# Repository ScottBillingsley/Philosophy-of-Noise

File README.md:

# Philosophy-of-Noise-readme.txt

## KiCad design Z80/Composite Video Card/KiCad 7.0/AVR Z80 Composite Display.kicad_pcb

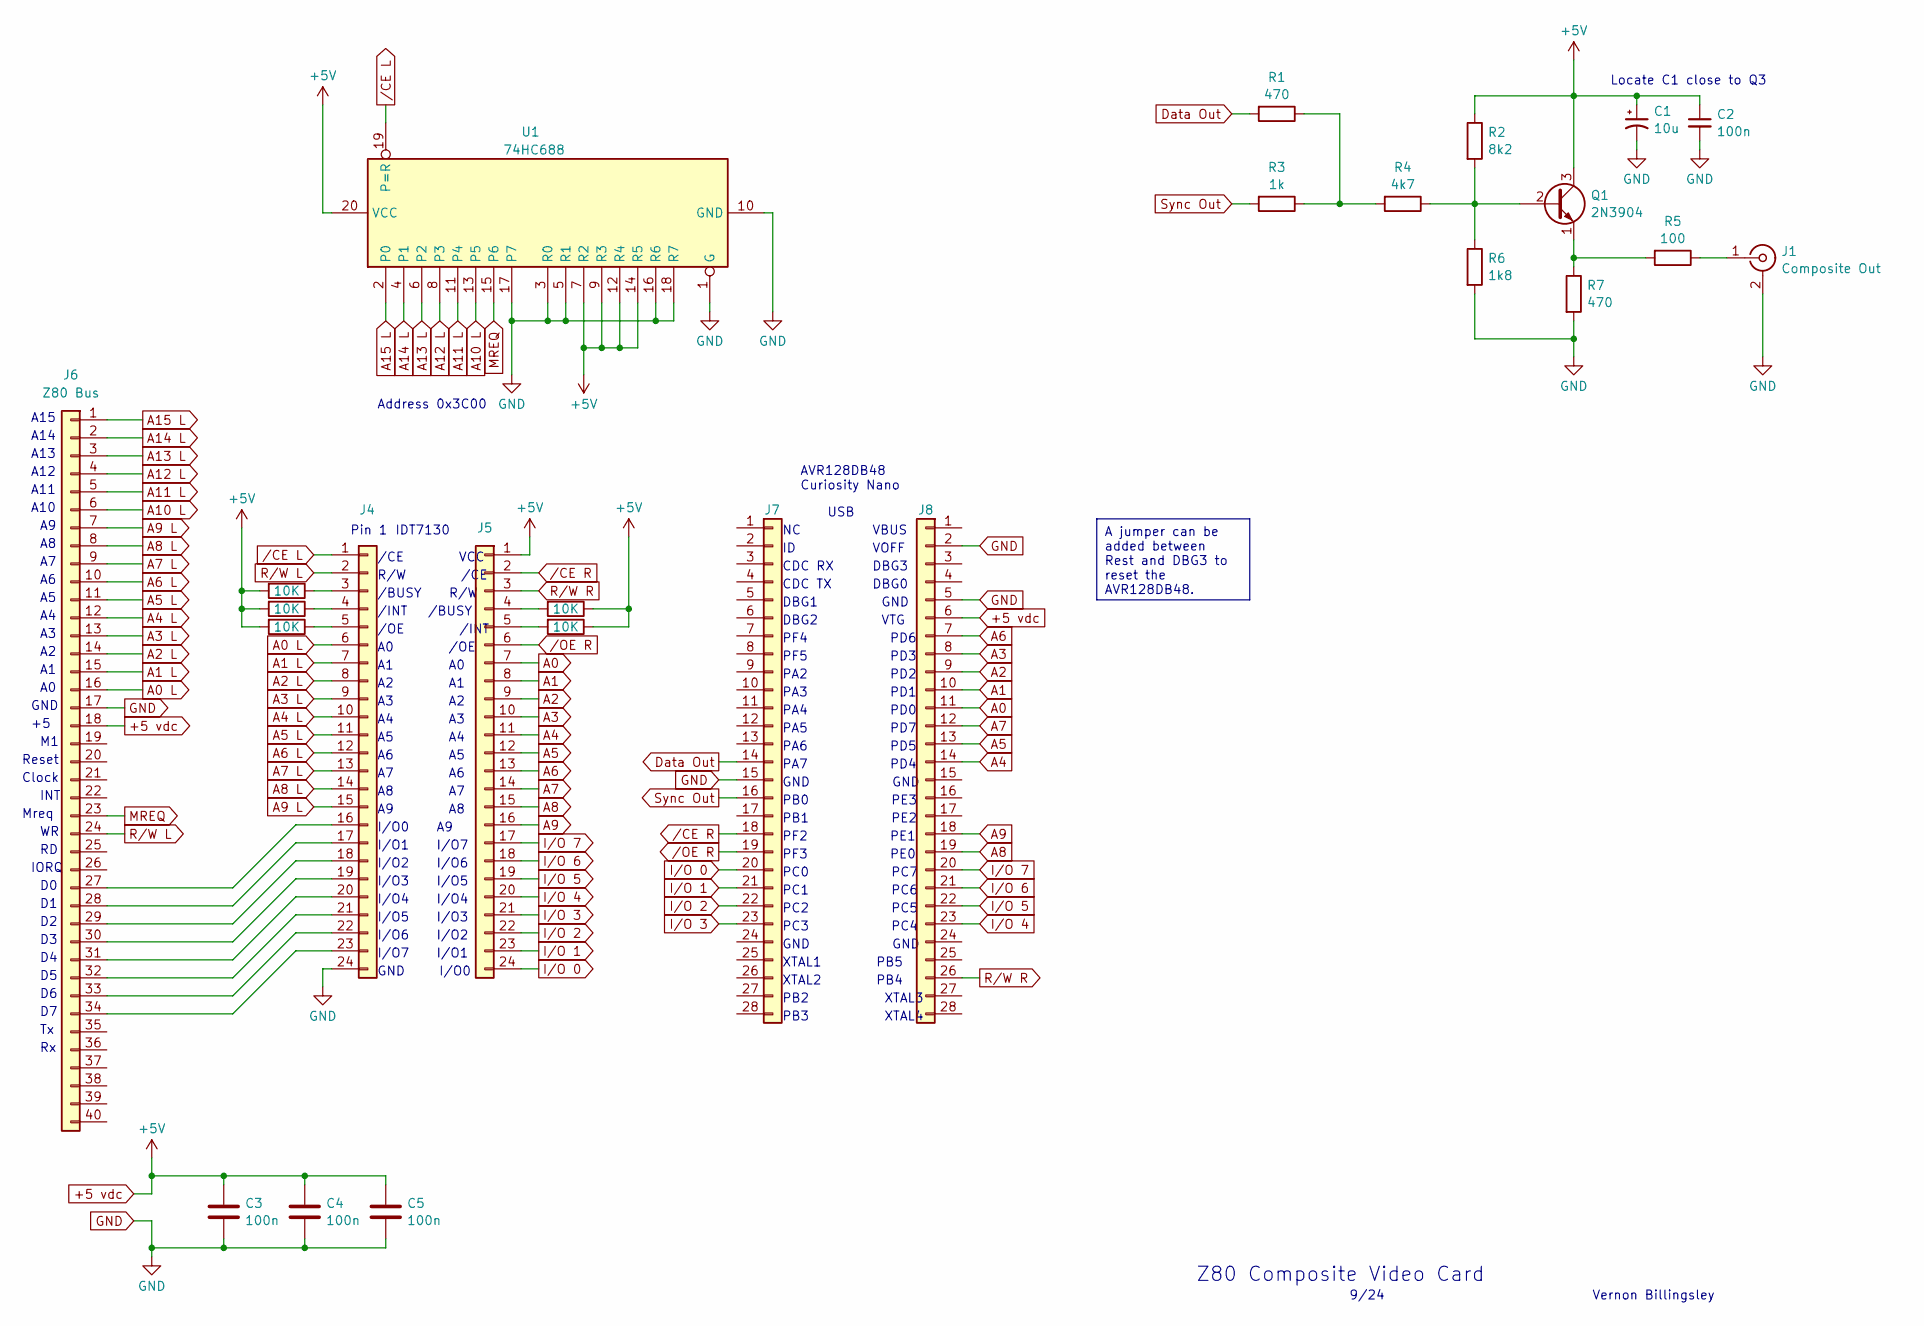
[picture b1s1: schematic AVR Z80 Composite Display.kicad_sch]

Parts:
C1: 10u; CP_Radial_D5.0mm_P2.50mm
C2: 100n; C_Rect_L7.0mm_W2.5mm_P5.00mm
C3, C4, C5: 100n; C_1206_3216Metric_Pad1.33x1.80mm_HandSolder
J1: Composite Out; PinHeader_1x02_P2.54mm_Vertical
J4, J5: Conn_01x24; PinHeader_1x24_P2.54mm_Vertical
J6: Z80 Bus; PinHeader_1x40_P2.54mm_Vertical
J7, J8: Conn_01x28; PinHeader_1x28_P2.54mm_Vertical
Q1: 2N3904; TO-92_Inline
R1, R7: 470; R_Axial_DIN0207_L6.3mm_D2.5mm_P7.62mm_Horizontal
R2: 8k2; R_Axial_DIN0207_L6.3mm_D2.5mm_P7.62mm_Horizontal
R3: 1k; R_Axial_DIN0207_L6.3mm_D2.5mm_P7.62mm_Horizontal
R4: 4k7; R_Axial_DIN0207_L6.3mm_D2.5mm_P7.62mm_Horizontal
R5: 100; R_Axial_DIN0207_L6.3mm_D2.5mm_P7.62mm_Horizontal
R6: 1k8; R_Axial_DIN0207_L6.3mm_D2.5mm_P7.62mm_Horizontal
R8, R9, R10, R11, R12: 10K; R_Axial_DIN0207_L6.3mm_D2.5mm_P7.62mm_Horizontal
U1: 74HC688; DIP-20_W7.62mm

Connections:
+5 vdc: C1.1, C2.1, C3.1, C4.1, C5.1, J5.1, J6.18, J8.6, Q1.3 (C), R2.1, R8.2, R9.2, R10.1, R11.2, R12.1, U1.7 (R2), U1.9 (R3), U1.12 (R4), U1.14 (R5), U1.20 (VCC)
A0: J5.7, J8.11
A0 L: J4.6, J6.16
A1: J5.8, J8.10
A1 L: J4.7, J6.15
A2: J5.9, J8.9
A2 L: J4.8, J6.14
A3: J5.10, J8.8
A3 L: J4.9, J6.13
A4: J5.11, J8.14
A4 L: J4.10, J6.12
A5: J5.12, J8.13
A5 L: J4.11, J6.11
A6: J5.13, J8.7
A6 L: J4.12, J6.10
A7: J5.14, J8.12
A7 L: J4.13, J6.9
A8: J5.15, J8.19
A8 L: J4.14, J6.8
A9: J5.16, J8.18
A9 L: J4.15, J6.7
A10 L: J6.6, U1.13 (P5)
A11 L: J6.5, U1.11 (P4)
A12 L: J6.4, U1.8 (P3)
A13 L: J6.3, U1.6 (P2)
A14 L: J6.2, U1.4 (P1)
A15 L: J6.1, U1.2 (P0)
Data Out: J7.14, R1.2
GND: C1.2, C2.2, C3.2, C4.2, C5.2, J1.2 (Ext), J4.24, J6.17, J7.15, J8.2, J8.5, R6.2, R7.2, U1.1 (G), U1.3 (R0), U1.5 (R1), U1.10 (GND), U1.16 (R6), U1.17 (P7), U1.18 (R7)
I/O 0: J5.24, J7.20
I/O 1: J5.23, J7.21
I/O 2: J5.22, J7.22
I/O 3: J5.21, J7.23
I/O 4: J5.20, J8.23
I/O 5: J5.19, J8.22
I/O 6: J5.18, J8.21
I/O 7: J5.17, J8.20
MREQ: J6.23, U1.15 (P6)
unnamed: J1.1 (In), R5.1
unnamed: J4.3, R8.1
unnamed: J4.4, R9.1
unnamed: J4.5, R11.1
unnamed: J4.16, J6.27
unnamed: J4.17, J6.28
unnamed: J4.18, J6.29
unnamed: J4.19, J6.30
unnamed: J4.20, J6.31
unnamed: J4.21, J6.32
unnamed: J4.22, J6.33
unnamed: J4.23, J6.34
unnamed: J5.4, R10.2
unnamed: J5.5, R12.2
unnamed: Q1.2 (B), R2.2, R4.1, R6.1
unnamed: Q1.1 (E), R5.2, R7.1
unnamed: R1.1, R3.1, R4.2
R/W L: J4.2, J6.24
R/W R: J5.3, J8.26
Sync Out: J7.16, R3.2
/CE L: J4.1, U1.19 (P=R)
/CE R: J5.2, J7.18
/OE R: J5.6, J7.19

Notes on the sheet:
A jumper can be added between Rest and DBG3 to reset the AVR128DB48.
GND GND
A13
GND
DBG3
Clock
A8 A7
PA4 PD0
PF5 PD3
PC2 PC5
PB3 XTAL4
I/O1 I/O7
/OE /INT
A2 A1
PC3 PC4
A0 /OE
GND I/O0
9/24
USB
PF3 PE0
A11
/INT /BUSY
VOFF
I/O5 I/O3
Mreq
PB2 XTAL3
AVR128DB48 Curiosity Nano
/BUSY R/W
A1 A0
PC1 PC6
A10
IDT7130
PA6 PD5
A6 A5
A14
DBG2
XTAL1 PB5
I/O0 A9
Z80 Composite Video Card
PC0 PC7

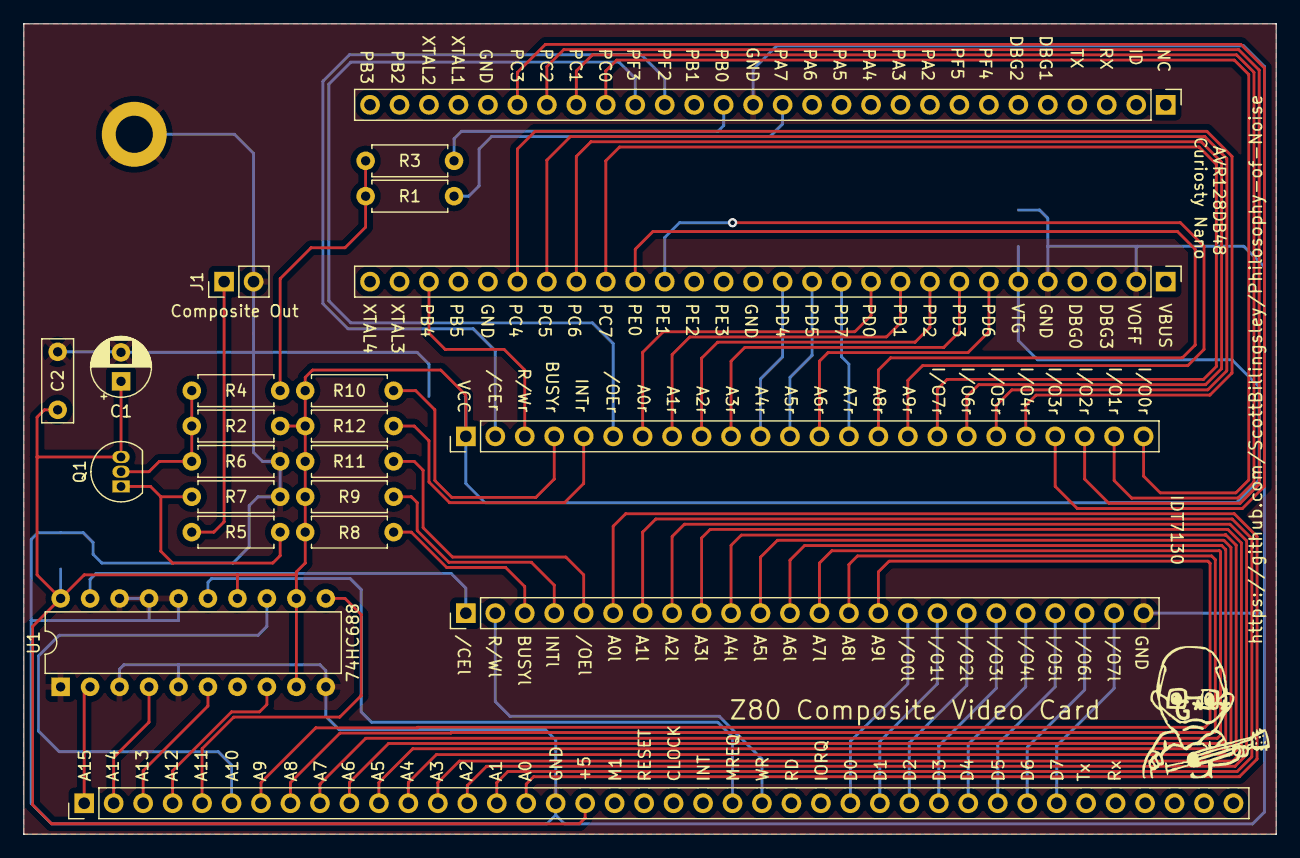
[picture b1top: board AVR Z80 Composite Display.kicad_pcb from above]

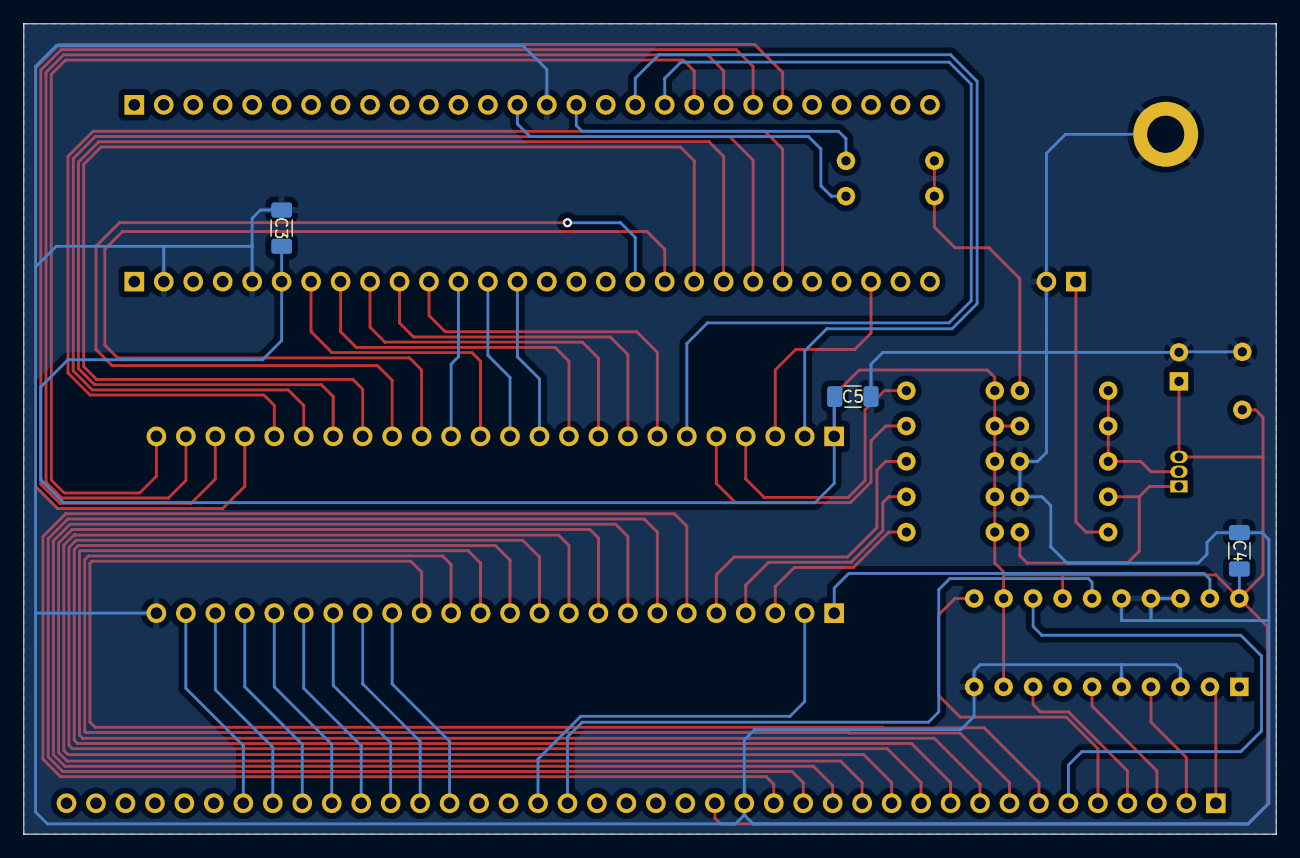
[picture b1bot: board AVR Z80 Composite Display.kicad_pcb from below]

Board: 2 copper layers, 108.0 x 69.8 mm, 25 parts (3 on the bottom side), 61 nets.

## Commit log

2024-10-07 Rename Shooting Star.lst to Shooting Stars.lst
2025-03-28 Create images
